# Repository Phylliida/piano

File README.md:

# piano

Open hardware modular hexagonal piano, inspired by the Lumatone.

It is built from identical tiles of 8 x 5 keys on a hex lattice. Each key is
an MX-style magnetic switch over a Hall-effect sensor, so the tile reads how
far every key is pressed. Tiles snap together edge to edge, in any
arrangement, and a short cable under each seam carries power and data. A hub
(not designed yet) will plug into any free edge, take power in and give USB
out: MIDI or raw key data.

## Status

| part | state |
|---|---|
| tile PCB | routed, DRC clean, not ordered yet. [`pcb/README.md`](pcb/README.md) lists what to verify before ordering |
| tile case | generated and checked on its solids, not printed yet |
| hub | not designed |
| firmware | not written |

## Where things are

| file | what |
|---|---|
| `tilegeom.py` | every dimension the board and the case share. Run it to check them |
| `tile_circuit.py` | the tile's circuit as data |
| `gen_lib.py`, `gen_sch.py`, `gen_pcb.py` | make the KiCad library, schematic and (once) the board |
| `route_board.py`, `pcbroute.py` | the board's routing as a script |
| `pcb/` | the KiCad project, and its README with the pin map for the firmware |
| `gen_case.py` | builds the printed case from `tilegeom.py` |
| `cad/` | its output: STLs ready to print, and two drawings |
| `HE60_NOTES.md` | notes on the sensing chain (sections 1 to 5) |

`TILE95.md`, `COST_ESTIMATE.md`, `gen_tile.py`, `gen_hex_board.py`,
`bom_model.py` and `kicad/` belong to earlier designs and contradict this one.

## The case

A printed tray (key plate, ribs, walls) and a printed bottom cover per tile.
No screws.

- **PCB:** drops into the tray from below. The switch pegs locate it.
- **Cover:** tuck its W edge over the lip on the W wall, then press its E edge
  down until the two catch beams click over the bumps on the E wall. Posts on
  the cover press the PCB against the ribs. To open it, pry a beam's tip out
  at its notch in the E wall, beside the E cable channel.
- **Tile to tile:** dovetail rails on a tile's E and N walls run in slots in
  the next tile's W and S walls. One snap latch per seam stops the tile
  lifting off again.
- **Cables:** at every port the cover and both walls are cut away, so the
  cable lies in an open channel from one tile's header to the next one's. It
  goes in from underneath, with the covers on.

### Putting tiles together

1. Start with the south-west tile, keys up, on a table.
2. Lower each further tile straight down beside it: its W and S slots slide
   over the rails of the tiles already there, and the latches click. Tiles
   only go together downward, never sideways.
3. Work outward to the north and east. A tile cannot be lowered into a place
   that already has a tile to its north or east.
4. Turn the keyboard over and plug a 50 mm JST GH 6-pin cable across each
   seam ([`pcb/README.md`](pcb/README.md) says how to measure the 50 mm).
   Either way round works.

To take it apart, unplug the cables and pull tiles straight up, starting at
the north-east. A firm pull releases a latch.

The rails carry a tile's weight, the latches only hold it down. So lift an
assembly by its south-west tile or from underneath; lifted by another tile,
the ones south and west of it hang on their latches.

### Printing

`cad/` holds the parts in their print orientation: the tray upside down
(plate on the bed), the cover with its posts up. Print without support. One
tile's tray is 168 x 134 mm.

1. **`plate_test.stl`**, a 1.5 mm plate. Check that switches clip in, measure
   the two spans `gen_case.py` prints, and pass their ratio as `--xy-scale` if
   your printer shrinks.
2. **The coupons:** `coupon_tray.stl` twice, `coupon_cover.stl` and
   `coupon_pcb_dummy.stl` once. A coupon is a 2 x 4-key tile with every snap
   feature of the full one. Check the cover's catch on one, then join the two
   trays E to W and N to S.
3. **`tray.stl`, `cover.stl`** and, until boards exist, **`pcb_dummy.stl`**:
   a plastic stand-in with the board's outline, thickness and peg holes.

If a fit is off, change the number in `tilegeom.py` and run `gen_case.py`
again:

| symptom | constant |
|---|---|
| rails too tight or too loose in their slots | `RAIL_CLEAR` (0.15 mm) |
| latch lets go too easily, or will not let go | `LATCH_ANGLE` (50 degrees; higher holds harder) |
| latch does not click in | `LATCH_BITE` (0.6 mm), `LATCH_PLAY` (0.2 mm) |

`LIP_W` and `CATCH_D` must stay as they are: the board's outline is built on
them.

Not yet tried in plastic, so expect a round or two on the coupons. Known
soft spots:

- The latch beams stand upright on the bed and bend across their layers,
  the weak direction. They strain 0.7 %, which PLA should take; PETG is
  the safer choice.
- The W lip is a 1.5 mm ledge with nothing under it. Its underside, which
  the cover rests on, will come out rough.
- The dovetails' sharp edges print rounded, which loosens them slightly.

### Building the case files

```
python3 tilegeom.py     # check the geometry
python3 gen_case.py     # check the fits on the solids, write cad/
```

`gen_case.py` needs `manifold3d` and `numpy`. It refuses to write anything
unless the solids show that neighbouring tiles clear each other, that a tile
can be lowered onto its neighbours' rails, that the latches and dovetails
then hold it, and that the cover and the PCB fit.

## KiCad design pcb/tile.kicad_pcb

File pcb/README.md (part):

# Tile PCB (8 x 5 keys)

Made by scripts, not drawn by hand, and fully routed: KiCad's DRC reports
0 errors and 0 unrouted connections.

- **Schematic:** regenerated from `tile_circuit.py` on every run. Don't edit
  `tile.kicad_sch` by hand: the next run overwrites it.
- **Board:** no longer regenerated. `gen_pcb.py` placed the parts once and
  now refuses to run, because it would throw the routing away. Change the
  board in KiCad, or with a script that edits it in place, as
  `place_ports.py`, `remove_leds.py` and `route_board.py` do.

| file | made by | what |
|---|---|---|
| `../tile_circuit.py` | you | every part and connection, as data |
| `../tilegeom.py` | you | every position the board and the printed case share |
| `tile.kicad_sym`, `tile.pretty/` | `gen_lib.py` | the MCU and sensor symbols and the switch footprint (plus LED ones, unused since the LEDs were removed) |
| `tile.kicad_sch` | `gen_sch.py` | the schematic |
| `tile.kicad_pcb`, `tile.kicad_pro` | `gen_pcb.py`, then by hand, then `route_board.py` | every part placed, ground planes, track widths per net (`gen_pcb.py`); each key's two stubs and the power block (by hand); every other track and via (`route_board.py`) |
| `../route_board.py`, `../pcbroute.py` | you | the routing as a script, and the small router it uses |

After changing `tile_circuit.py`:

```
../kpython.sh ../gen_lib.py && ../kpython.sh ../gen_sch.py
```

To route again, after a change to `route_board.py` or to a pin in the
circuit, start from the board as it was routed by hand. The script refuses
a board it has already routed:

```
git show 991aaaf:pcb/tile.kicad_pcb > tile.kicad_pcb
../kpython.sh ../route_board.py
```

Its `nets` stage gives the pads the nets `tile_circuit.py` names. The later
stages name pins and coordinates, so a moved signal means adapting the stage
that routes it, and a new part has to be placed first.

`kpython.sh` and `kcli.sh` run KiCad's Python and `kicad-cli` on one core, at
low priority. Their paths are NixOS store paths, so edit them on another machine.

## What each run proves

- **Schematic:** KiCad exports its own netlist of the generated file, and it
  must equal `tile_circuit.nets()` net for net (81 nets). Any ERC error
  stops the run. Reruns keep every symbol's UUID, so a routed board stays
  linked to its schematic.
- **Pins:** every IC connection names the pin it expects (`("U2", "3", "IN")`),
  and generation stops if the symbol disagrees. This caught the TVS diode's
  pin names on the first run.
- **Board:** `route_board.py` checks every track and via against the
  net classes' clearances as it adds them, then runs DRC with schematic
  parity in a fresh process. Result: 0 errors, 0 parity issues, 0 unrouted
  connections. The 72 silkscreen warnings (reference texts in tight spots)
  were there before routing.
- **Audit:** an independent review on 2026-10-11 checked every IC's
  pin-to-pad mapping against its datasheet (all correct), plus the circuit,
  part heights and the fit with the case. Its findings are fixed below,
  except the ones listed under "Before ordering".

## The board

- **2 layers** (cheaper). This works because every part sits on the back, so
  the front is almost entirely free. HE60 routes 67 keys on 2 layers.
  - **B.Cu (bottom):** every part, each sensor's track to its mux, the
    sensors' supply, and a ground fill around them.
  - **F.Cu (top, switch side):** no parts. It is the ground plane, cut only
    by what has to cross the back's tracks: the mux lines up the middle, VIN,
    `+3V3` to the MCU, the port data lines and eight short supply hops.
  - To switch back to 4 layers (solid inner ground and power planes, easier
    routing, higher cost), set `LAYERS = 4` in `gen_pcb.py`.
- **Under each key:** the sensor is centred under the switch stem. Its 100n
  (supply) and 4.7n (output) capacitors sit beside it. Every key is identical.
- **Power:** VIN (7–20 V) → TVS → U2, an AP63201 buck set to 3.72 V →
  U3, a TLV75733 linear regulator → `+3V3` for the MCU → FB1, a ferrite →
  `+3.3VA` for VDDA, the sensors and the muxes.
  - The 40 sensors draw about 250 mA. Dropping that from 5 V in one linear
    regulator would cost about 0.45 W of heat next to them, so the buck
    takes most of the drop and U3 burns only about 0.15 W.
  - VDD and VDDA come from the same regulator, as the datasheet requires,
    within 15 mV of each other.
- **No LEDs** (removed 2026-10-20, `remove_leds.py` took them off the routed
  board). A tile draws about 1.2 W, so a 400-key build (10 tiles) needs
  12–13 W: about 0.85 A at 15 V, well inside the 2 A one port can bring in.
  Lit keys would have needed several times that.
- **Circles:** the case's cover posts press there. Keep them free of parts.
  Rule areas make DRC enforce this.
- **Ports:** one JST GH header per edge, each opening straight toward its wall
  slot. Their spots are data in `tilegeom.PORT_SPOTS` (found by a search
  over this board), so the case's slots and the board always agree;
  `place_ports.py` moves the parts to match.
  - **Cables:** E and W share a height; N and S share column 5. Partner
    headers' openings are 50 mm apart across the seam, so a 50 mm GH 6-pin
    cable runs straight from one to the other, in the 5 mm under the boards.
    The case leaves that whole run open from below: the cover is cut away
    from each header to its edge and both walls are open down to the floor.
    The cable passes under one key on the way, between or beside its switch
    pegs.
  - **Cable length:** "50 mm" should mean 50 mm between the two plugs'
    fronts. Some listings measure the wire alone (a little slack, fine) or
    the whole cable end to end (about 5 mm short). Check the listing's
    drawing.
  - **Pinout:** `VIN, GND, A, B, GND, VIN`. It's symmetric, so a reversed
    cable cannot short power, and a ground wire separates each data wire
    from VIN. The MCU's `TRPSWAP` bit fixes swapped data pins in firmware.
  - **Plugging in:** snap the tiles together, turn the keyboard over and
    plug the cable in from underneath. The covers stay on. Straight or
    reversed both work.

## How it is routed

`route_board.py` works in stages, each a short function that names its
tracks' coordinates or searches for them:

| stage | what it adds |
|---|---|
| `lanes`, `lanes3` | Each sensor's output to its mux, on the back. A mux lies in the band between two key rows; the lanes run along the band, side by side, into its pins. The channel order was chosen so that none cross. Row 3's mux stands across its band, beside the MCU, and its lanes come round it. |
| `bus` | The three select lines and the five mux outputs, up the middle of the board on the front. |
| `supply` | `+3.3VA` as a ladder on the back, 0.5 mm wide: a spine down the west and east edges, four rungs between the key rows, a short drop to each sensor and mux. The outermost keys at the north and south edges, which no rung reaches, get theirs over the front. |
| `vin` | VIN between the four ports and to the TVS, 1 mm wide: west to east on the front, a stem down the middle to the S port. Two vias wherever it changes layer, because the current of every tile further on passes through. |
| `uarts` | Two data lines per port, through the 220R resistors. |
| `mcu` | `+3V3`, the crystal, reset, BOOT0, the debug pads, the pull-downs. |
| `gnd` | A via to the front plane at every ground pad: 172 of them. Larger ones (0.8 mm) at the ports, the TVS and the regulators' capacitors. |
| `ties` | 182 more vias between the two ground fills. The tracks cut the back's fill into pieces; each piece gets a via wherever it is more than 8 mm from its next one, if one fits. |

The power block keeps its hand routing, and the ports stand where
`place_ports.py` put them.

One weak spot, accepted: the ground pins of AM4 (row 3's mux) and of two
small parts beside it reach the plane over a 5 mm long, 0.25 mm wide track
to the via of one of the MCU's ground pins, because tracks wall the front in there. A 4051
draws microamps.

## Pin map, for the firmware

`tile_circuit.py` is the truth (`SELECT_PINS`, `ADC_PINS`, `ADC_CHANNEL`,
`CHANNEL_OF_COL`, `UARTS`); this is a copy.

- **Keys:** column 0 is the west one, row 0 the south one. Key
  `HE(5 * column + row + 1)`.
- **Selects**, shared by the five muxes: S0 = PB0, S1 = PC5, S2 = PC4.
  S0 is the lowest bit.
- **Mux outputs:** one select value reads one key of every row.

  | row | mux | MCU pin | ADC1 channel |
  |---|---|---|---|
  | 0 | AM1 | PA4 | 4 |
  | 1 | AM2 | PA5 | 5 |
  | 2 | AM3 | PA6 | 6 |
  | 3 | AM4 | PB1 | 9 |
  | 4 | AM5 | PA7 | 7 |

- **Select value for each column:**

  | column | 0 | 1 | 2 | 3 | 4 | 5 | 6 | 7 |
  |---|---|---|---|---|---|---|---|---|
  | rows 0, 1, 2, 4 | 6 | 7 | 4 | 5 | 2 | 3 | 1 | 0 |
  | row 3 | 0 | 1 | 3 | 2 | 5 | 4 | 7 | 6 |

- **Ports** (TX, RX): W = USART2 (PA2, PA3), N = USART6 (PC6, PC7),
  E = UART8 (PC8, PC9), S = USART3 (PC10, PC11). The pins' IOMUX numbers
  are in the reference manual, chapter 6.
- **Debug pads J1**, pad 1 to 6: +3V3, BOOT0, SWCLK, NRST, SWDIO, GND.

## Before ordering: not yet verified

- **LCSC part numbers:**
  - Still to pick:
    - AP63201WU-7
    - SMAJ20A
    - the FNR4030S 10 µH (≥ 1 A) inductor
    - BLM18PG221SN1D
    - MT9102ET
    - SN74LV4051APWR
  - Every capacitor value now carries its voltage rating (`10u/50V`). Keep it
    when choosing parts.
  - Genuine JST GH SM06B-GHS-TB is out of stock. The XYECONN clone
    `C51940119` is stocked, but I haven't read its datasheet.
- **Input voltage:** keep VIN at or below 19–20 V. The SMAJ20A starts
  conducting just above 20 V, which is fine for 12 V and 15 V supplies.
- **Current through a port:** each GH contact is rated 1 A with 26 AWG wire
  (less with the thinner wire most ready-made cables use), so a port carries
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
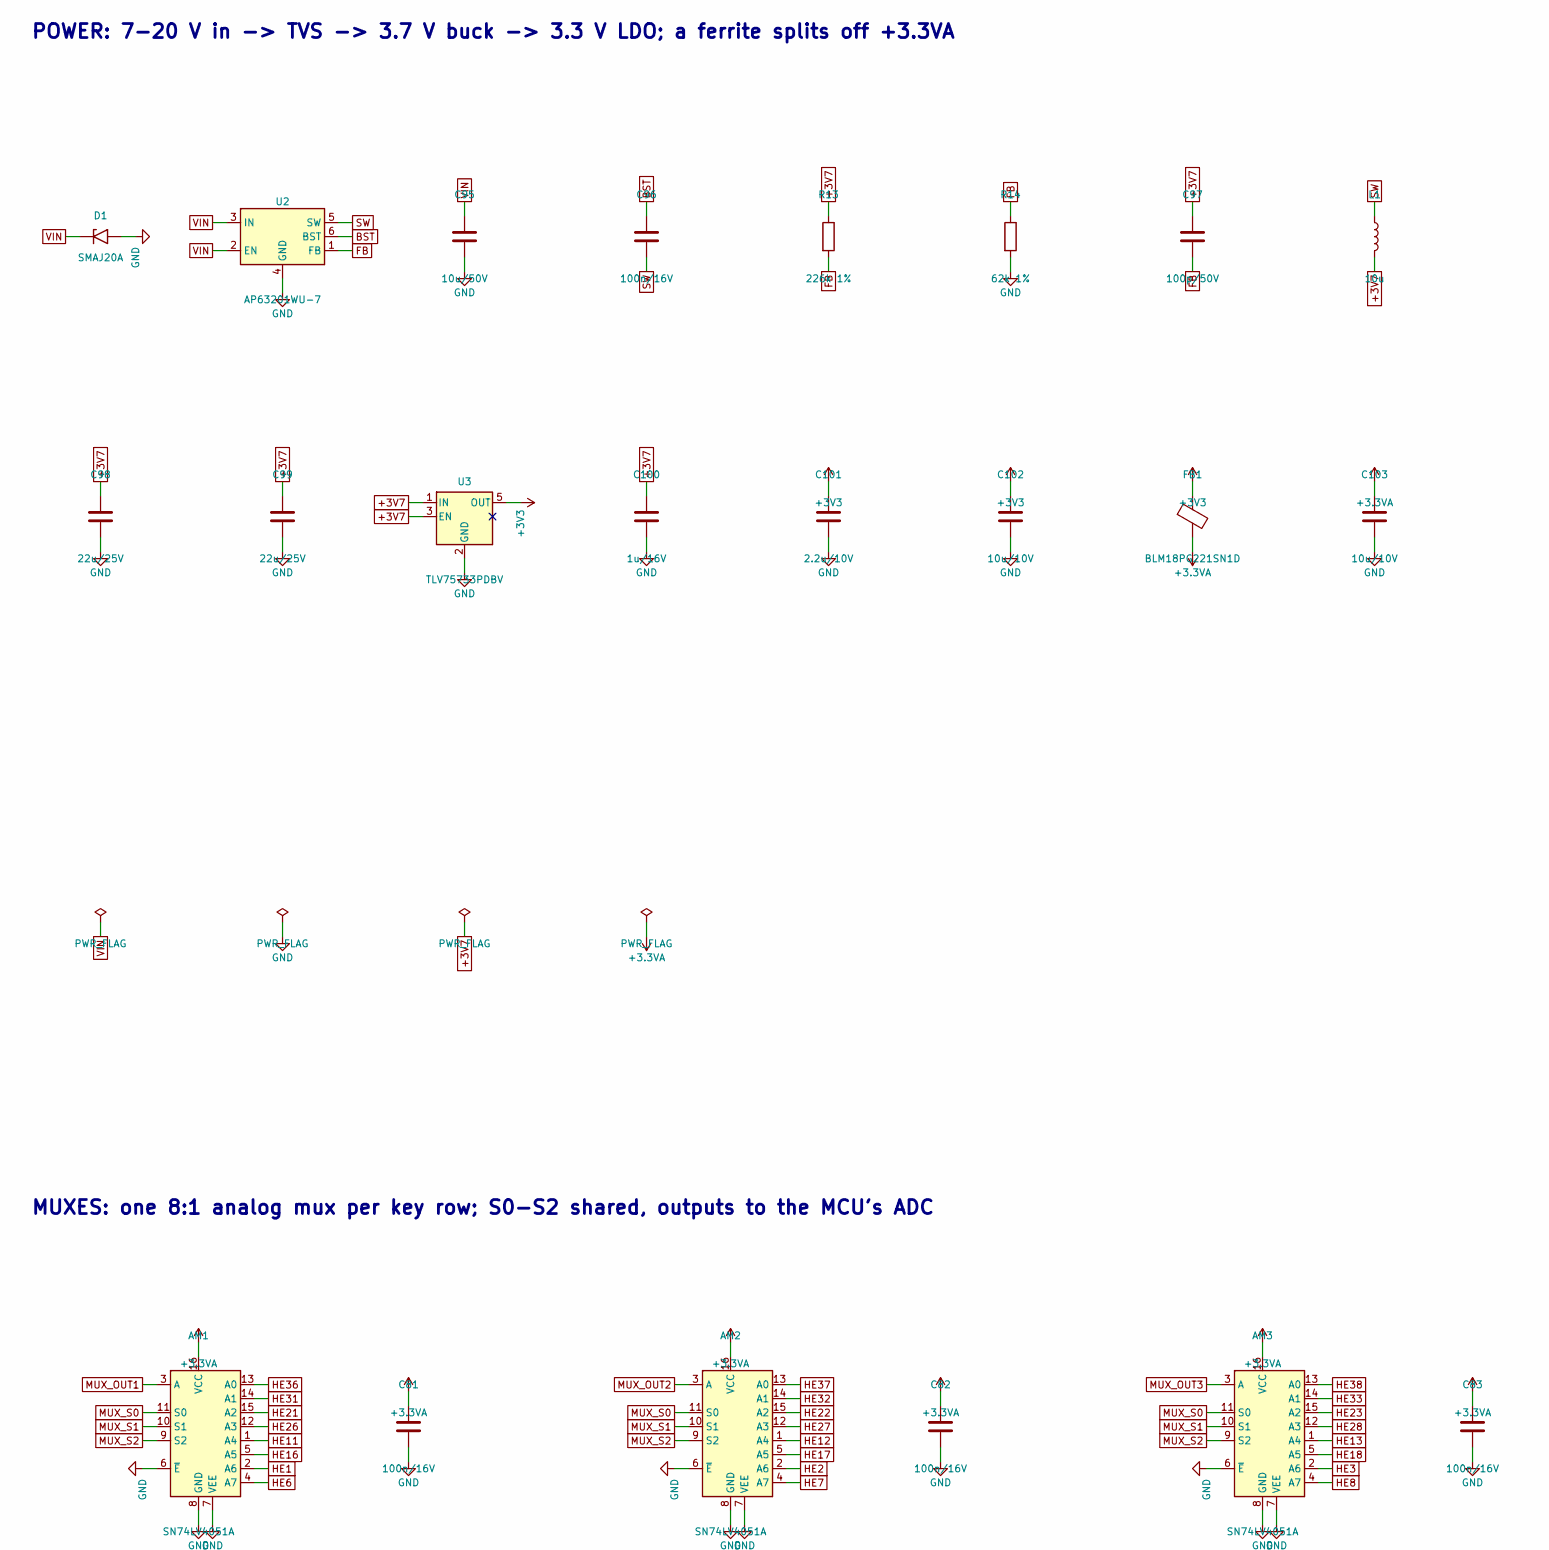
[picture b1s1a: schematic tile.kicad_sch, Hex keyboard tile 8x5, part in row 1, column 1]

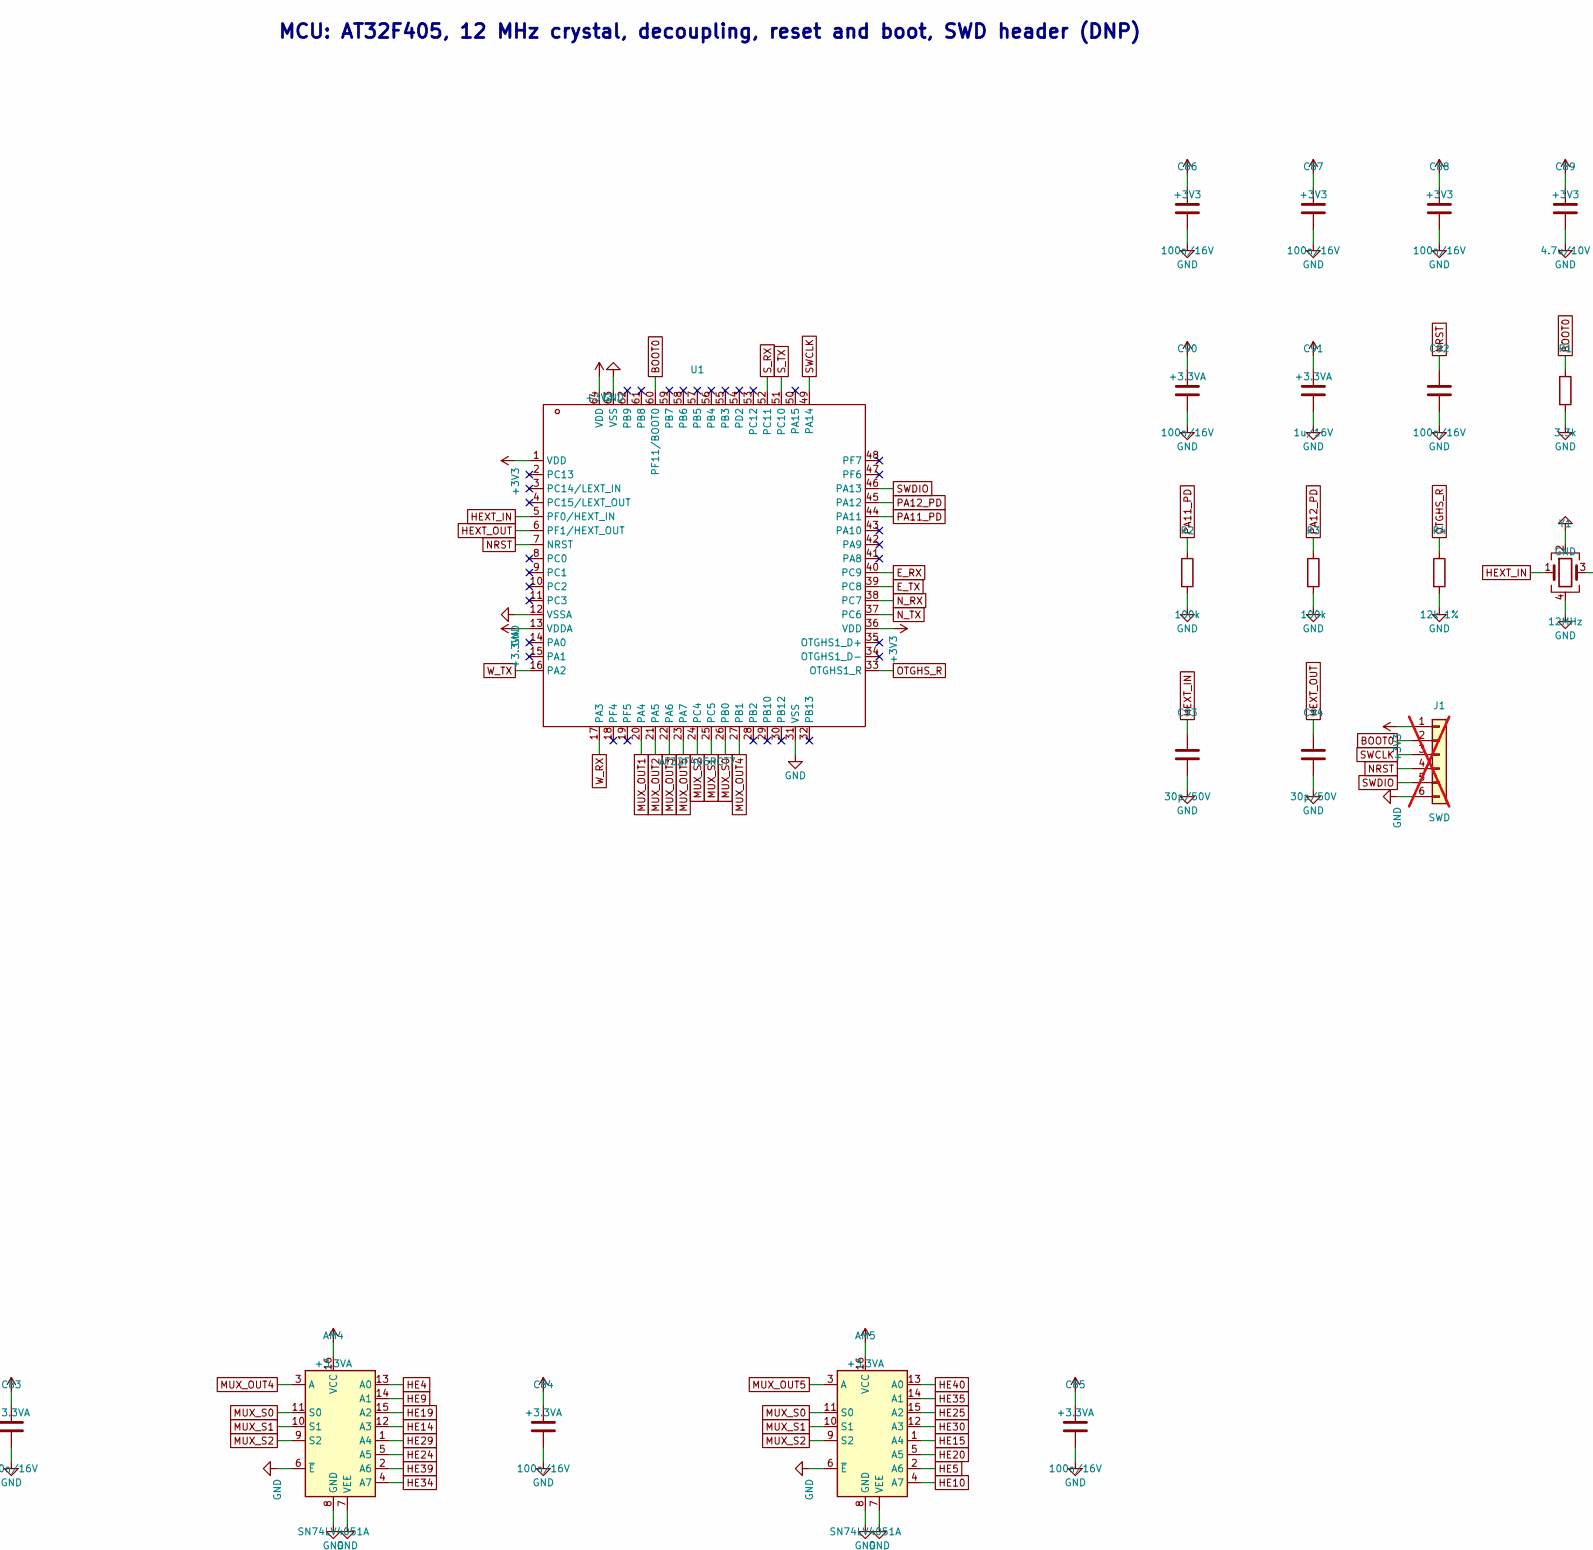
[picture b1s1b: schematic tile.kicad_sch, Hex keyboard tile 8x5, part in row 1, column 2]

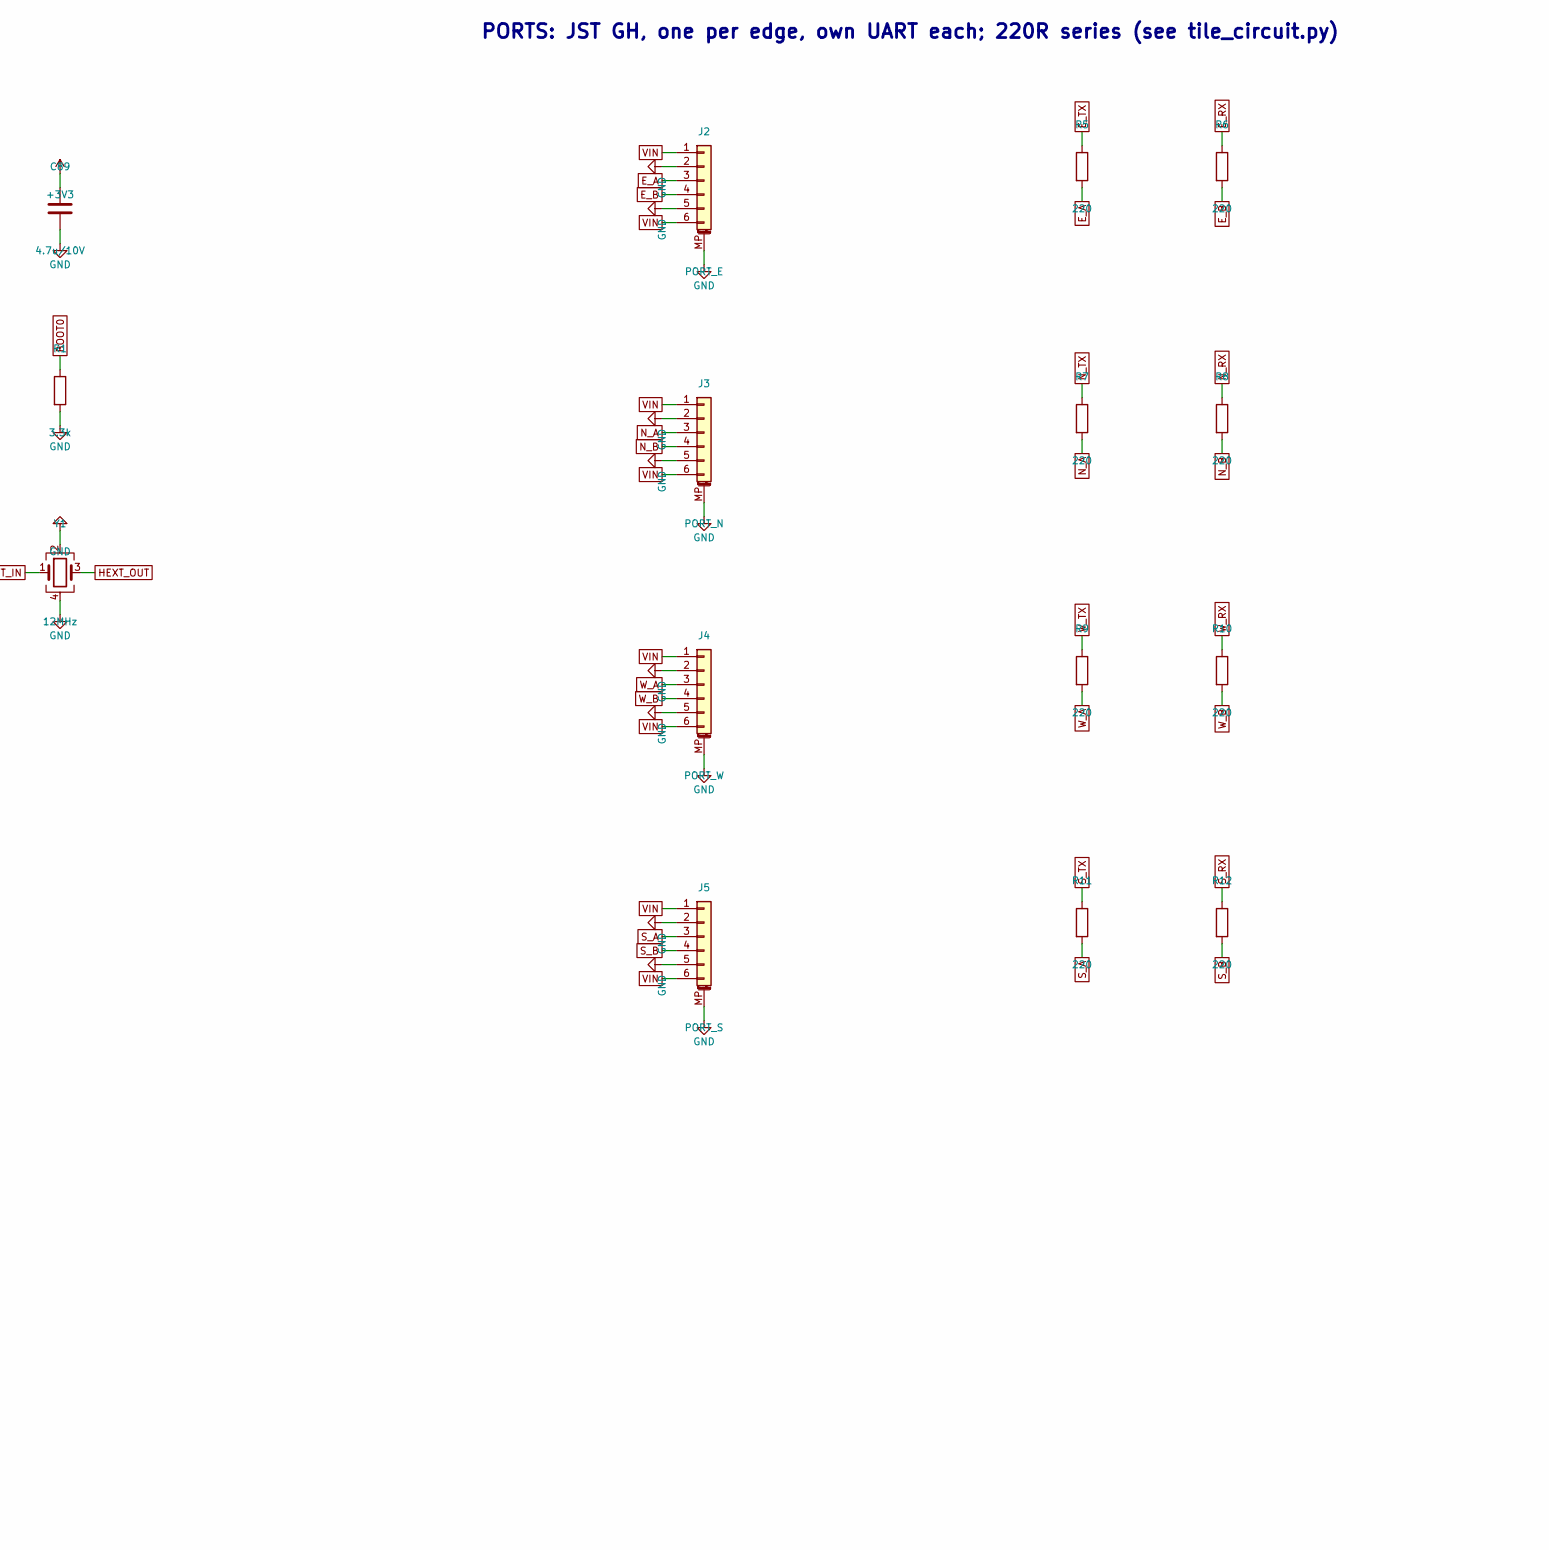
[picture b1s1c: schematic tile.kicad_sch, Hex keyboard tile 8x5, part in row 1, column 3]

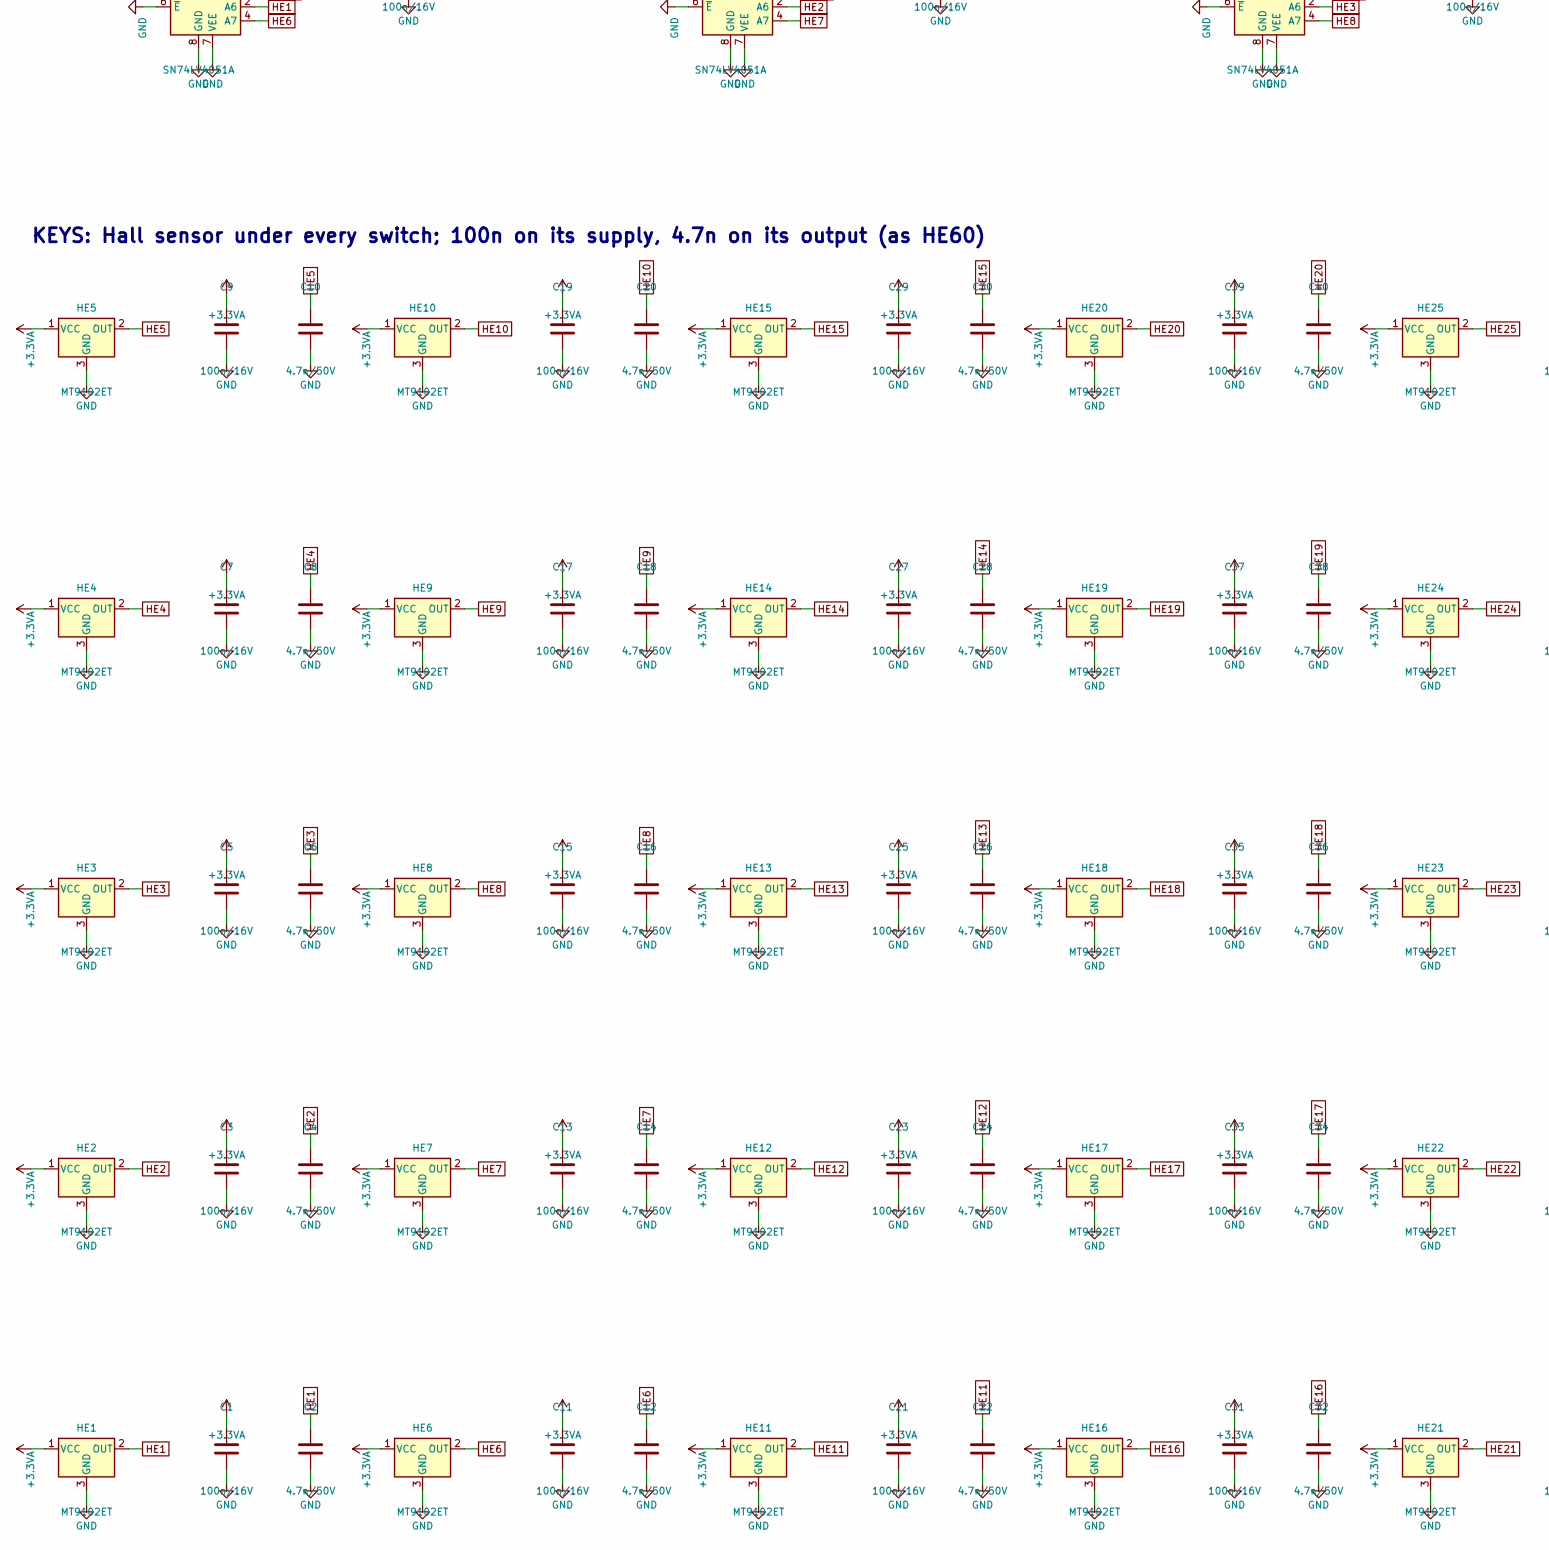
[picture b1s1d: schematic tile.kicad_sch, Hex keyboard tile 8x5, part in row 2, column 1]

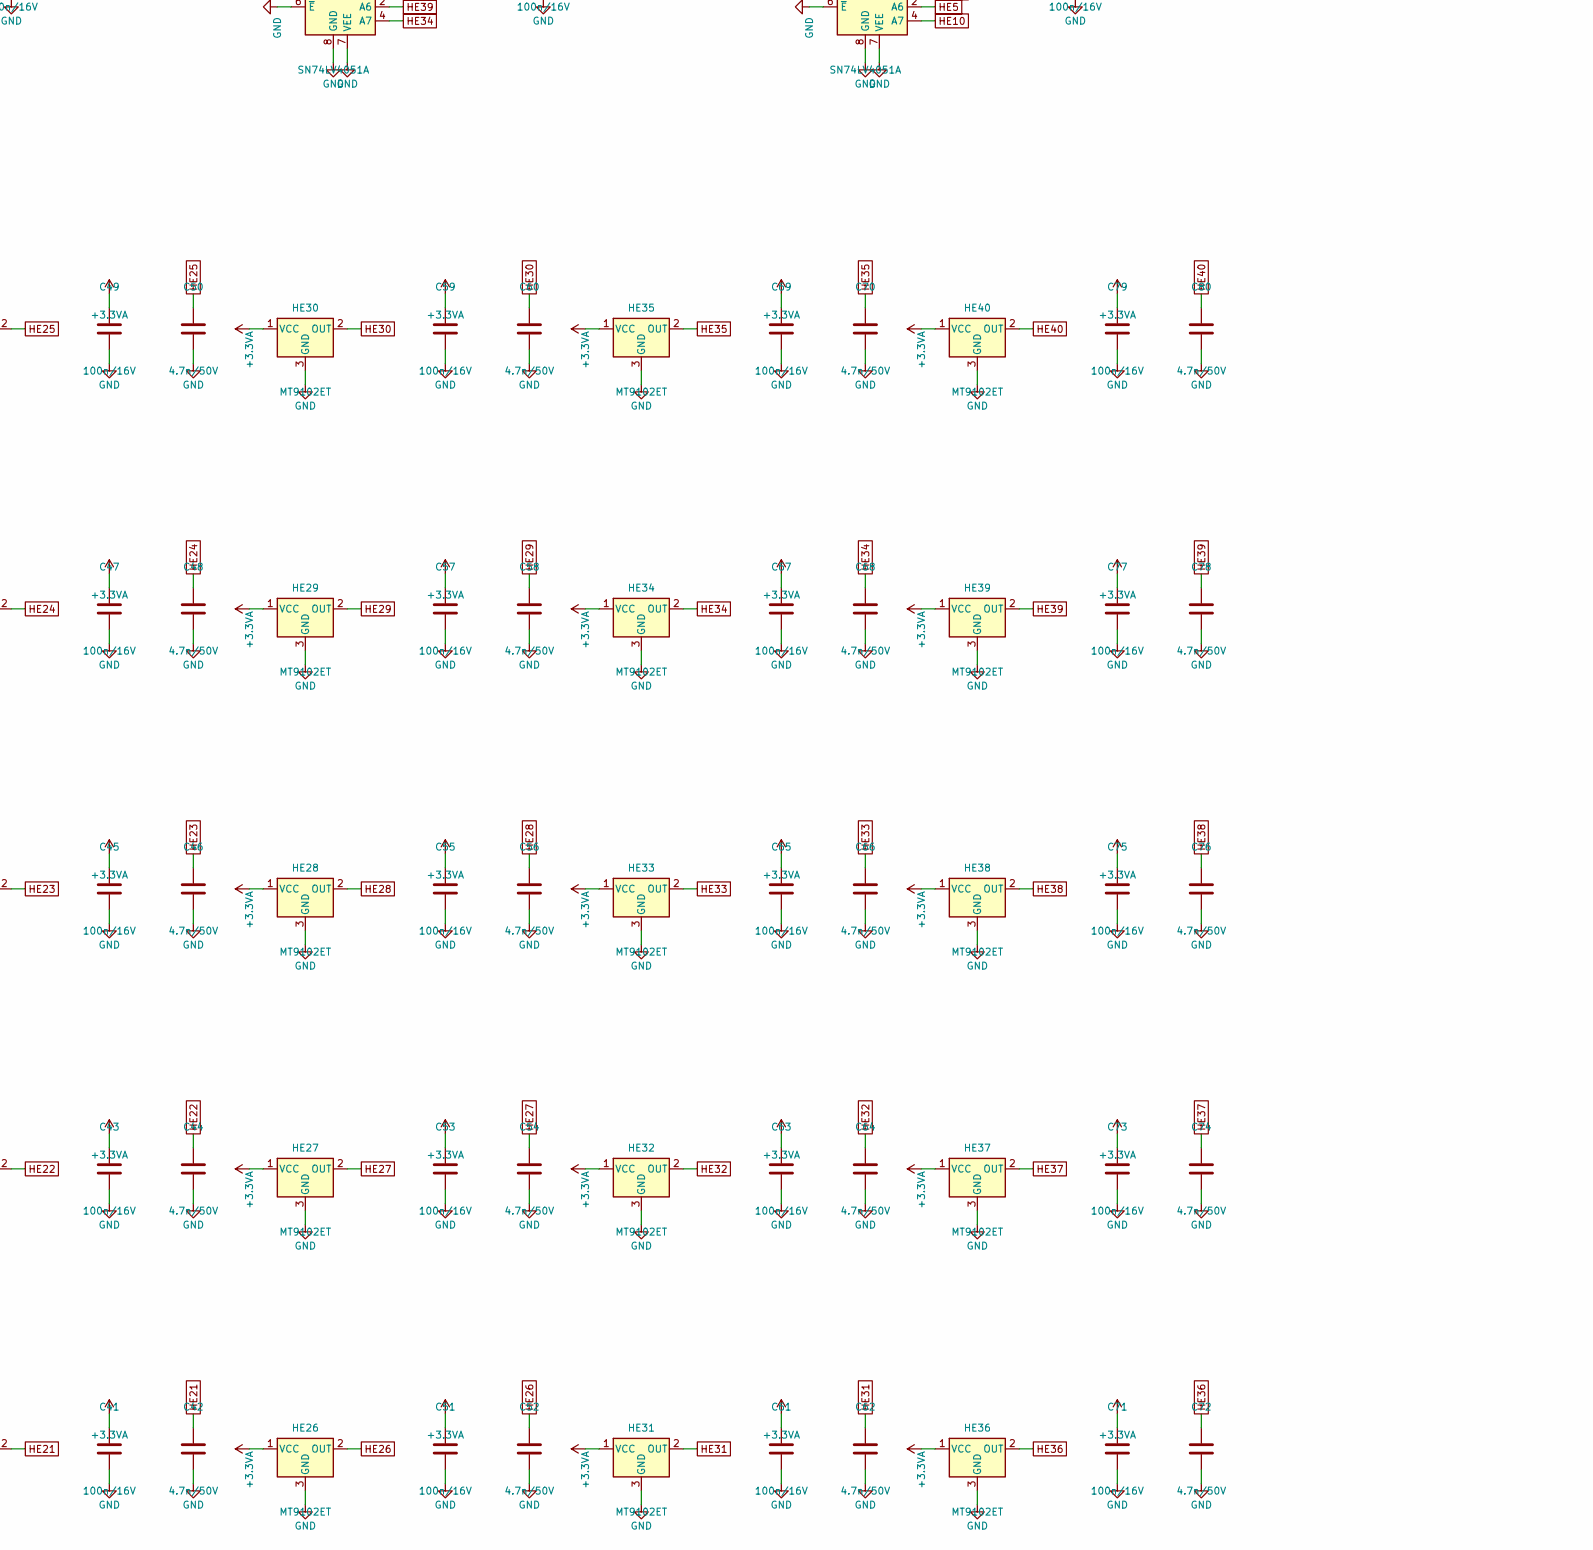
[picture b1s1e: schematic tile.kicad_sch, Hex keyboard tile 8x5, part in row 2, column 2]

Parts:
AM1, AM2, AM3, AM4, AM5: SN74LV4051A; TSSOP-16_4.4x5mm_P0.65mm; MPN SN74LV4051APWR
C1, C3, C5, C7, C9, C11, C13, C15, C17, C19, C21, C23, C25, C27, C29, C31, C33, C35, C37, C39, C41, C43, C45, C47, C49, C51, C53, C55, C57, C59, C61, C63, C65, C67, C69, C71, C73, C75, C77, C79, C81, C82, C83, C84, C85, C86, C87, C88, C90, C92, C96: 100n/16V; C_0402_1005Metric
C2, C4, C6, C8, C10, C12, C14, C16, C18, C20, C22, C24, C26, C28, C30, C32, C34, C36, C38, C40, C42, C44, C46, C48, C50, C52, C54, C56, C58, C60, C62, C64, C66, C68, C70, C72, C74, C76, C78, C80: 4.7n/50V; C_0402_1005Metric
C89: 4.7u/10V; C_0603_1608Metric
C91, C100: 1u/16V; C_0402_1005Metric
C93, C94: 30p/50V; C_0402_1005Metric
C95: 10u/50V; C_1206_3216Metric
C97: 100p/50V; C_0402_1005Metric
C98, C99: 22u/25V; C_0805_2012Metric
C101: 2.2u/10V; C_0603_1608Metric
C102, C103: 10u/10V; C_0805_2012Metric
D1: SMAJ20A; D_SMA
FB1: BLM18PG221SN1D; L_0603_1608Metric; MPN BLM18PG221SN1D
HE1, HE2, HE3, HE4, HE5, HE6, HE7, HE8, HE9, HE10, HE11, HE12, HE13, HE14, HE15, HE16, HE17, HE18, HE19, HE20, HE21, HE22, HE23, HE24, HE25, HE26, HE27, HE28, HE29, HE30, HE31, HE32, HE33, HE34, HE35, HE36, HE37, HE38, HE39, HE40: MT9102ET; SOT-23-3
J1: SWD; PinHeader_1x06_P2.54mm_Vertical_SMD_Pin1Left; not fitted
J2: PORT_E; JST_GH_SM06B-GHS-TB_1x06-1MP_P1.25mm_Horizontal; MPN SM06B-GHS-TB
J3: PORT_N; JST_GH_SM06B-GHS-TB_1x06-1MP_P1.25mm_Horizontal; MPN SM06B-GHS-TB
J4: PORT_W; JST_GH_SM06B-GHS-TB_1x06-1MP_P1.25mm_Horizontal; MPN SM06B-GHS-TB
J5: PORT_S; JST_GH_SM06B-GHS-TB_1x06-1MP_P1.25mm_Horizontal; MPN SM06B-GHS-TB
L1: 10u; L_Changjiang_FNR4030S; MPN FNR4030S100MT
R1: 3.3k; R_0402_1005Metric
R2, R3: 100k; R_0402_1005Metric
R4: 12k 1%; R_0402_1005Metric
R5, R6, R7, R8, R9, R10, R11, R12: 220; R_0402_1005Metric
R13: 226k 1%; R_0402_1005Metric
R14: 62k 1%; R_0402_1005Metric
U1: AT32F405RCT7; LQFP-64_10x10mm_P0.5mm; MPN AT32F405RCT7
U2: AP63201WU-7; TSOT-23-6
U3: TLV75733PDBV; SOT-23-5
Y1: 12MHz; Crystal_SMD_3225-4Pin_3.2x2.5mm; MPN X322512MSB4SI

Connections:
+3.3VA: AM1.16 (VCC), AM2.16 (VCC), AM3.16 (VCC), AM4.16 (VCC), AM5.16 (VCC), C1.1, C3.1, C5.1, C7.1, C9.1, C11.1, C13.1, C15.1, C17.1, C19.1, C21.1, C23.1, C25.1, C27.1, C29.1, C31.1, C33.1, C35.1, C37.1, C39.1, C41.1, C43.1, C45.1, C47.1, C49.1, C51.1, C53.1, C55.1, C57.1, C59.1, C61.1, C63.1, C65.1, C67.1, C69.1, C71.1, C73.1, C75.1, C77.1, C79.1, C81.1, C82.1, C83.1, C84.1, C85.1, C90.1, C91.1, C103.1, FB1.2, HE1.1 (VCC), HE2.1 (VCC), HE3.1 (VCC), HE4.1 (VCC), HE5.1 (VCC), HE6.1 (VCC), HE7.1 (VCC), HE8.1 (VCC), HE9.1 (VCC), HE10.1 (VCC), HE11.1 (VCC), HE12.1 (VCC), HE13.1 (VCC), HE14.1 (VCC), HE15.1 (VCC), HE16.1 (VCC), HE17.1 (VCC), HE18.1 (VCC), HE19.1 (VCC), HE20.1 (VCC), HE21.1 (VCC), HE22.1 (VCC), HE23.1 (VCC), HE24.1 (VCC), HE25.1 (VCC), HE26.1 (VCC), HE27.1 (VCC), HE28.1 (VCC), HE29.1 (VCC), HE30.1 (VCC), HE31.1 (VCC), HE32.1 (VCC), HE33.1 (VCC), HE34.1 (VCC), HE35.1 (VCC), HE36.1 (VCC), HE37.1 (VCC), HE38.1 (VCC), HE39.1 (VCC), HE40.1 (VCC), U1.13 (VDDA)
+3V3: C86.1, C87.1, C88.1, C89.1, C101.1, C102.1, FB1.1, J1.1, U1.1 (VDD), U1.36 (VDD), U1.64 (VDD), U3.5 (OUT)
+3V7: C97.1, C98.1, C99.1, C100.1, L1.2, R13.1, U3.1 (IN), U3.3 (EN)
BOOT0: J1.2, R1.1, U1.60 (PF11/BOOT0)
BST: C96.1, U2.6 (BST)
E_A: J2.3, R5.2
E_B: J2.4, R6.2
E_RX: R6.1, U1.40 (PC9)
E_TX: R5.1, U1.39 (PC8)
FB: C97.2, R13.2, R14.1, U2.1 (FB)
GND: AM1.6 (~E), AM1.7 (VEE), AM1.8 (GND), AM2.6 (~E), AM2.7 (VEE), AM2.8 (GND), AM3.6 (~E), AM3.7 (VEE), AM3.8 (GND), AM4.6 (~E), AM4.7 (VEE), AM4.8 (GND), AM5.6 (~E), AM5.7 (VEE), AM5.8 (GND), C1.2, C2.2, C3.2, C4.2, C5.2, C6.2, C7.2, C8.2, C9.2, C10.2, C11.2, C12.2, C13.2, C14.2, C15.2, C16.2, C17.2, C18.2, C19.2, C20.2, C21.2, C22.2, C23.2, C24.2, C25.2, C26.2, C27.2, C28.2, C29.2, C30.2, C31.2, C32.2, C33.2, C34.2, C35.2, C36.2, C37.2, C38.2, C39.2, C40.2, C41.2, C42.2, C43.2, C44.2, C45.2, C46.2, C47.2, C48.2, C49.2, C50.2, C51.2, C52.2, C53.2, C54.2, C55.2, C56.2, C57.2, C58.2, C59.2, C60.2, C61.2, C62.2, C63.2, C64.2, C65.2, C66.2, C67.2, C68.2, C69.2, C70.2, C71.2, C72.2, C73.2, C74.2, C75.2, C76.2, C77.2, C78.2, C79.2, C80.2, C81.2, C82.2, C83.2, C84.2, C85.2, C86.2, C87.2, C88.2, C89.2, C90.2, C91.2, C92.2, C93.2, C94.2, C95.2, C98.2, C99.2, C100.2, C101.2, C102.2, C103.2, D1.2 (A2), HE1.3 (GND), HE2.3 (GND), HE3.3 (GND), HE4.3 (GND), HE5.3 (GND), HE6.3 (GND), HE7.3 (GND), HE8.3 (GND), HE9.3 (GND), HE10.3 (GND), HE11.3 (GND), HE12.3 (GND), HE13.3 (GND), HE14.3 (GND), HE15.3 (GND), HE16.3 (GND), HE17.3 (GND), HE18.3 (GND), HE19.3 (GND), HE20.3 (GND), HE21.3 (GND), HE22.3 (GND), HE23.3 (GND), HE24.3 (GND), HE25.3 (GND), HE26.3 (GND), HE27.3 (GND), HE28.3 (GND), HE29.3 (GND), HE30.3 (GND), HE31.3 (GND), HE32.3 (GND), HE33.3 (GND), HE34.3 (GND), HE35.3 (GND), HE36.3 (GND), HE37.3 (GND), HE38.3 (GND), HE39.3 (GND), HE40.3 (GND), J1.6, J2.2, J2.5, J2.MP (MountPin), J3.2, J3.5, J3.MP (MountPin), J4.2, J4.5, J4.MP (MountPin), J5.2, J5.5, J5.MP (MountPin), R1.2, R2.2, R3.2, R4.2, R14.2, U1.12 (VSSA), U1.31 (VSS), U1.63 (VSS), U2.4 (GND), U3.2 (GND), Y1.2, Y1.4
HE1: AM1.2 (A6), C2.1, HE1.2 (OUT)
HE2: AM2.2 (A6), C4.1, HE2.2 (OUT)
HE3: AM3.2 (A6), C6.1, HE3.2 (OUT)
HE4: AM4.13 (A0), C8.1, HE4.2 (OUT)
HE5: AM5.2 (A6), C10.1, HE5.2 (OUT)
HE6: AM1.4 (A7), C12.1, HE6.2 (OUT)
HE7: AM2.4 (A7), C14.1, HE7.2 (OUT)
HE8: AM3.4 (A7), C16.1, HE8.2 (OUT)
HE9: AM4.14 (A1), C18.1, HE9.2 (OUT)
HE10: AM5.4 (A7), C20.1, HE10.2 (OUT)
HE11: AM1.1 (A4), C22.1, HE11.2 (OUT)
HE12: AM2.1 (A4), C24.1, HE12.2 (OUT)
HE13: AM3.1 (A4), C26.1, HE13.2 (OUT)
HE14: AM4.12 (A3), C28.1, HE14.2 (OUT)
HE15: AM5.1 (A4), C30.1, HE15.2 (OUT)
HE16: AM1.5 (A5), C32.1, HE16.2 (OUT)
HE17: AM2.5 (A5), C34.1, HE17.2 (OUT)
HE18: AM3.5 (A5), C36.1, HE18.2 (OUT)
HE19: AM4.15 (A2), C38.1, HE19.2 (OUT)
HE20: AM5.5 (A5), C40.1, HE20.2 (OUT)
HE21: AM1.15 (A2), C42.1, HE21.2 (OUT)
HE22: AM2.15 (A2), C44.1, HE22.2 (OUT)
HE23: AM3.15 (A2), C46.1, HE23.2 (OUT)
HE24: AM4.5 (A5), C48.1, HE24.2 (OUT)
HE25: AM5.15 (A2), C50.1, HE25.2 (OUT)
HE26: AM1.12 (A3), C52.1, HE26.2 (OUT)
HE27: AM2.12 (A3), C54.1, HE27.2 (OUT)
HE28: AM3.12 (A3), C56.1, HE28.2 (OUT)
HE29: AM4.1 (A4), C58.1, HE29.2 (OUT)
HE30: AM5.12 (A3), C60.1, HE30.2 (OUT)
HE31: AM1.14 (A1), C62.1, HE31.2 (OUT)
HE32: AM2.14 (A1), C64.1, HE32.2 (OUT)
HE33: AM3.14 (A1), C66.1, HE33.2 (OUT)
HE34: AM4.4 (A7), C68.1, HE34.2 (OUT)
HE35: AM5.14 (A1), C70.1, HE35.2 (OUT)
HE36: AM1.13 (A0), C72.1, HE36.2 (OUT)
HE37: AM2.13 (A0), C74.1, HE37.2 (OUT)
HE38: AM3.13 (A0), C76.1, HE38.2 (OUT)
HE39: AM4.2 (A6), C78.1, HE39.2 (OUT)
HE40: AM5.13 (A0), C80.1, HE40.2 (OUT)
HEXT_IN: C93.1, U1.5 (PF0/HEXT_IN), Y1.1
HEXT_OUT: C94.1, U1.6 (PF1/HEXT_OUT), Y1.3
MUX_OUT1: AM1.3 (A), U1.20 (PA4)
MUX_OUT2: AM2.3 (A), U1.21 (PA5)
MUX_OUT3: AM3.3 (A), U1.22 (PA6)
MUX_OUT4: AM4.3 (A), U1.27 (PB1)
MUX_OUT5: AM5.3 (A), U1.23 (PA7)
MUX_S0: AM1.11 (S0), AM2.11 (S0), AM3.11 (S0), AM4.11 (S0), AM5.11 (S0), U1.26 (PB0)
MUX_S1: AM1.10 (S1), AM2.10 (S1), AM3.10 (S1), AM4.10 (S1), AM5.10 (S1), U1.25 (PC5)
MUX_S2: AM1.9 (S2), AM2.9 (S2), AM3.9 (S2), AM4.9 (S2), AM5.9 (S2), U1.24 (PC4)
NRST: C92.1, J1.4, U1.7 (NRST)
N_A: J3.3, R7.2
N_B: J3.4, R8.2
N_RX: R8.1, U1.38 (PC7)
N_TX: R7.1, U1.37 (PC6)
OTGHS_R: R4.1, U1.33 (OTGHS1_R)
PA11_PD: R2.1, U1.44 (PA11)
PA12_PD: R3.1, U1.45 (PA12)
SW: C96.2, L1.1, U2.5 (SW)
SWCLK: J1.3, U1.49 (PA14)
SWDIO: J1.5, U1.46 (PA13)
S_A: J5.3, R11.2
S_B: J5.4, R12.2
S_RX: R12.1, U1.52 (PC11)
S_TX: R11.1, U1.51 (PC10)
VIN: C95.1, D1.1 (A1), J2.1, J2.6, J3.1, J3.6, J4.1, J4.6, J5.1, J5.6, U2.2 (EN), U2.3 (IN)
W_A: J4.3, R9.2
W_B: J4.4, R10.2
W_RX: R10.1, U1.17 (PA3)
W_TX: R9.1, U1.16 (PA2)

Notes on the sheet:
KEYS: Hall sensor under every switch; 100n on its supply, 4.7n on its output (as HE60)
MUXES: one 8:1 analog mux per key row; S0-S2 shared, outputs to the MCU's ADC
MCU: AT32F405, 12 MHz crystal, decoupling, reset and boot, SWD header (DNP)
PORTS: JST GH, one per edge, own UART each; 220R series (see tile_circuit.py)
POWER: 7-20 V in -> TVS -> 3.7 V buck -> 3.3 V LDO; a ferrite splits off +3.3VA

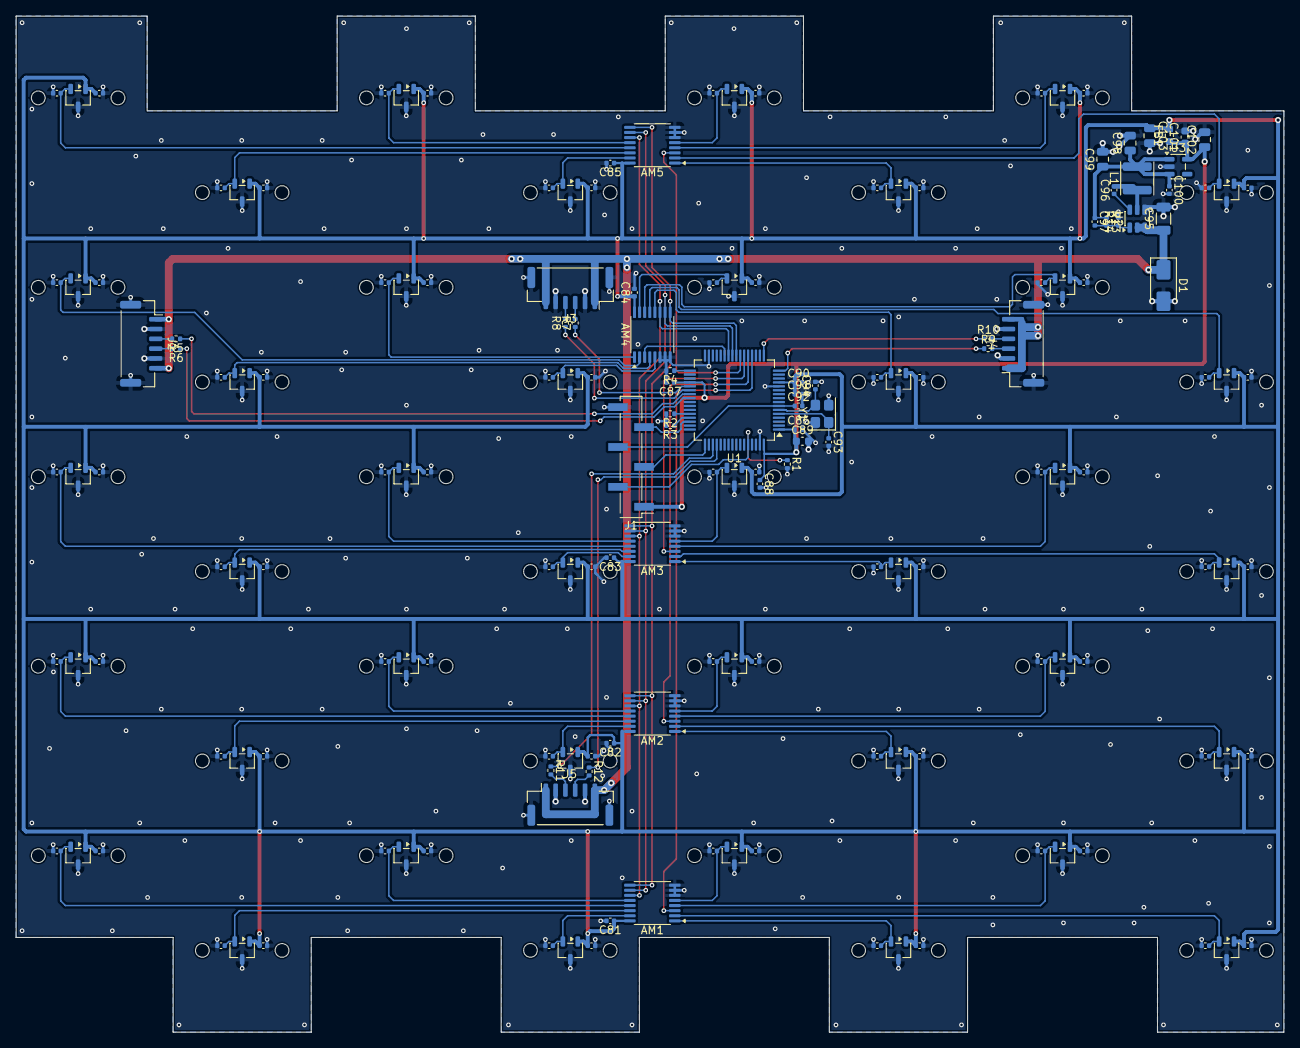
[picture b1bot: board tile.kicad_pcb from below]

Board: 2 copper layers, 161.6 x 129.5 mm, 214 parts (174 on the bottom side), 81 nets.

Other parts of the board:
SW1, SW2, SW3, SW4, SW5, SW6, SW7, SW8, SW9, SW10, SW11, SW12, SW13, SW14, SW15, SW16, SW17, SW18, SW19, SW20, SW21, SW22, SW23, SW24, SW25, SW26, SW27, SW28, SW29, SW30, SW31, SW32, SW33, SW34, SW35, SW36, SW37, SW38, SW39, SW40: MX_HE; MX-1U
